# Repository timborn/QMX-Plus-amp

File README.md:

# QMX-amp
The QMX+ is a very nice radio kit from QPR Labs
https://qrp-labs.com/

This amp is designed by Ron Taylor, WA7GIL.  It should fit inside the empty
space in the case.

doc/original-drawings shows the original design sketchs

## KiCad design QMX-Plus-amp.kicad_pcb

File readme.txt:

Mon Nov 11 14:53:17 MST 2024
----------------------------
Changed the name of this project to QMX-Plus-amp to remove confusion with QMX.

Mon Aug 19 12:31:12 MST 2024
----------------------------
- silk screen is landing in all kinds of unhelpful places
- RF paths need wide copper.  How wide?  Figure out netclasses
- +12V probably needs a wide path as well for all that current (HOW MUCH?)
- want K1 & K2 to be *identical* even tho they appear in multiple schematic
  pages.  I want the control signals on one, and the RF paths on another.
  So far all I get are complaints about duplicate symbols, even when I 
  copy / paste special.

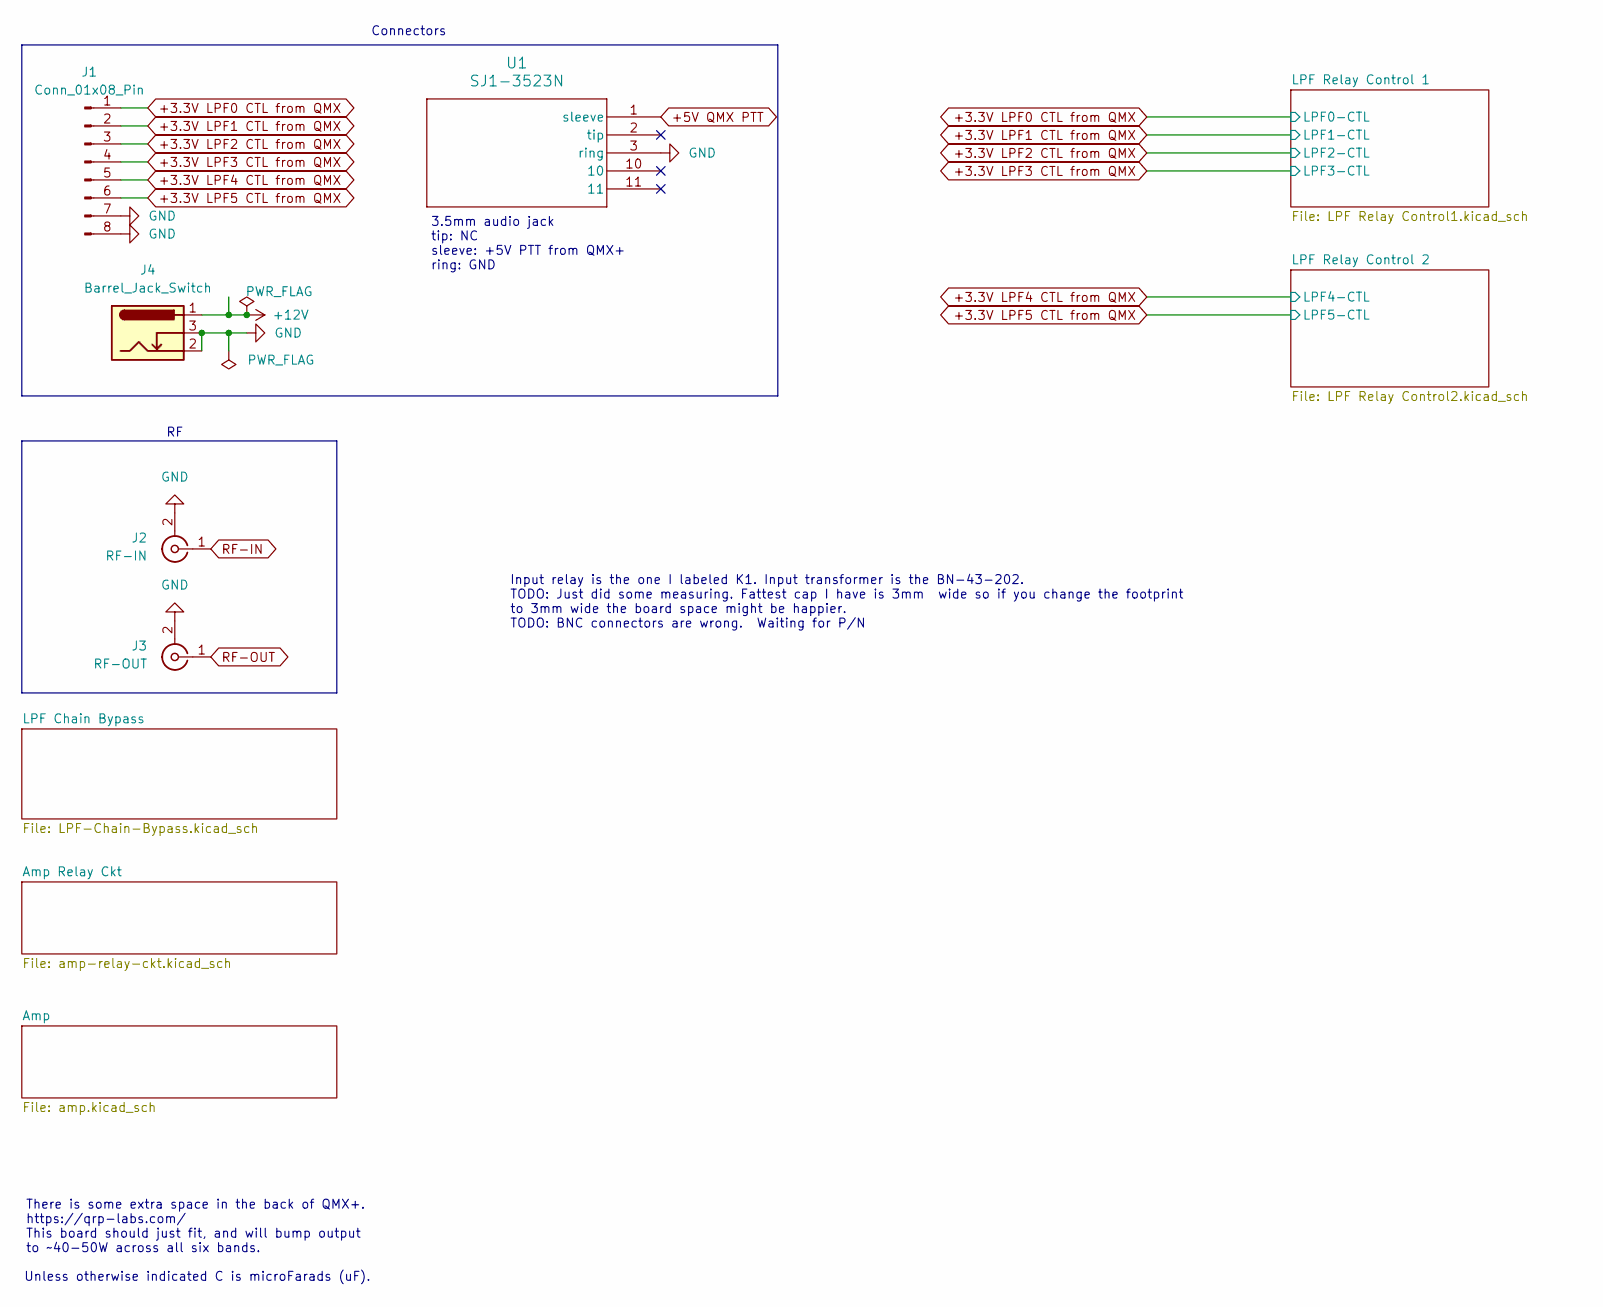
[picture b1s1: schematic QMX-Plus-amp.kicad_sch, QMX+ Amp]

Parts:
J1: Conn_01x08_Pin; PinHeader_1x08_P1.00mm_Horizontal
J2: RF-IN; BNC_Amphenol_B6252HB-NPP3G-50_Horizontal
J3: RF-OUT; BNC_Amphenol_B6252HB-NPP3G-50_Horizontal
J4: Barrel_Jack_Switch; BarrelJack_Horizontal
U1: SJ1-3523N; SJ1-3523N_CUD

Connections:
+3.3V LPF0 CTL from QMX: J1.1; also elsewhere on the board
+3.3V LPF1 CTL from QMX: J1.2; also elsewhere on the board
+3.3V LPF2 CTL from QMX: J1.3; also elsewhere on the board
+3.3V LPF3 CTL from QMX: J1.4; also elsewhere on the board
+3.3V LPF4 CTL from QMX: J1.5; also elsewhere on the board
+3.3V LPF5 CTL from QMX: J1.6; also elsewhere on the board
+5V QMX PTT: U1.1 (sleeve); also elsewhere on the board
+12V: J4.1; also elsewhere on the board
GND: J1.7, J1.8, J2.2 (Ext), J3.2 (Ext), J4.2, J4.3, U1.3 (ring); also elsewhere on the board
RF-IN: J2.1 (In); also elsewhere on the board
RF-OUT: J3.1 (In); also elsewhere on the board

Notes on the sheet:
Unless otherwise indicated C is microFarads (uF).
Connectors
Input relay is the one I labeled K1. Input transformer is the BN-43-202. TODO: Just did some measuring. Fattest cap I have is 3mm wide so if you change the footprint to 3mm wide the board space might be happier. TODO: BNC connectors are wrong. Waiting for P/N
3.5mm audio jack tip: NC sleeve: +5V PTT from QMX+ ring: GND
There is some extra space in the back of QMX+. https://qrp-labs.com/ This board should just fit, and will bump output to ~40-50W across all six bands.

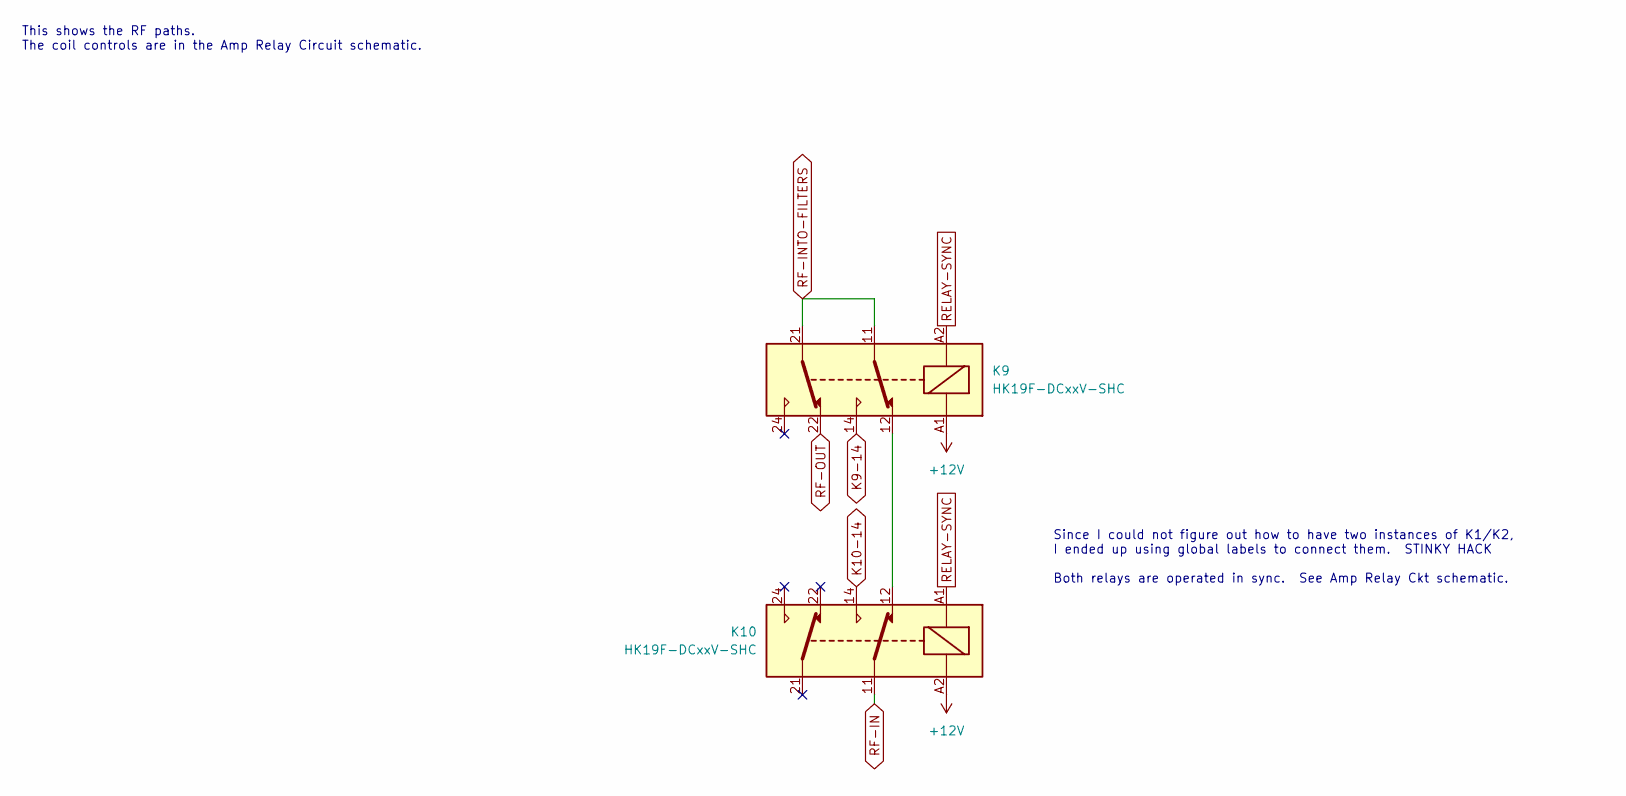
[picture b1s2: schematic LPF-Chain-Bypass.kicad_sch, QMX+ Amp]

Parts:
K9, K10: HK19F-DCxxV-SHC; Relay_DPDT_Finder_30.22

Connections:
+12V: K9.A1, K10.A2; also elsewhere on the board
K9-14: K9.14; also elsewhere on the board
K10-14: K10.14; also elsewhere on the board
unnamed: K9.12, K10.12
RELAY-SYNC: K9.A2, K10.A1; also elsewhere on the board
RF-IN: K10.11; also elsewhere on the board
RF-INTO-FILTERS: K9.11, K9.21; also elsewhere on the board
RF-OUT: K9.22; also elsewhere on the board

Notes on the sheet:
Since I could not figure out how to have two instances of K1/K2, I ended up using global labels to connect them. STINKY HACK Both relays are operated in sync. See Amp Relay Ckt schematic.
This shows the RF paths. The coil controls are in the Amp Relay Circuit schematic.

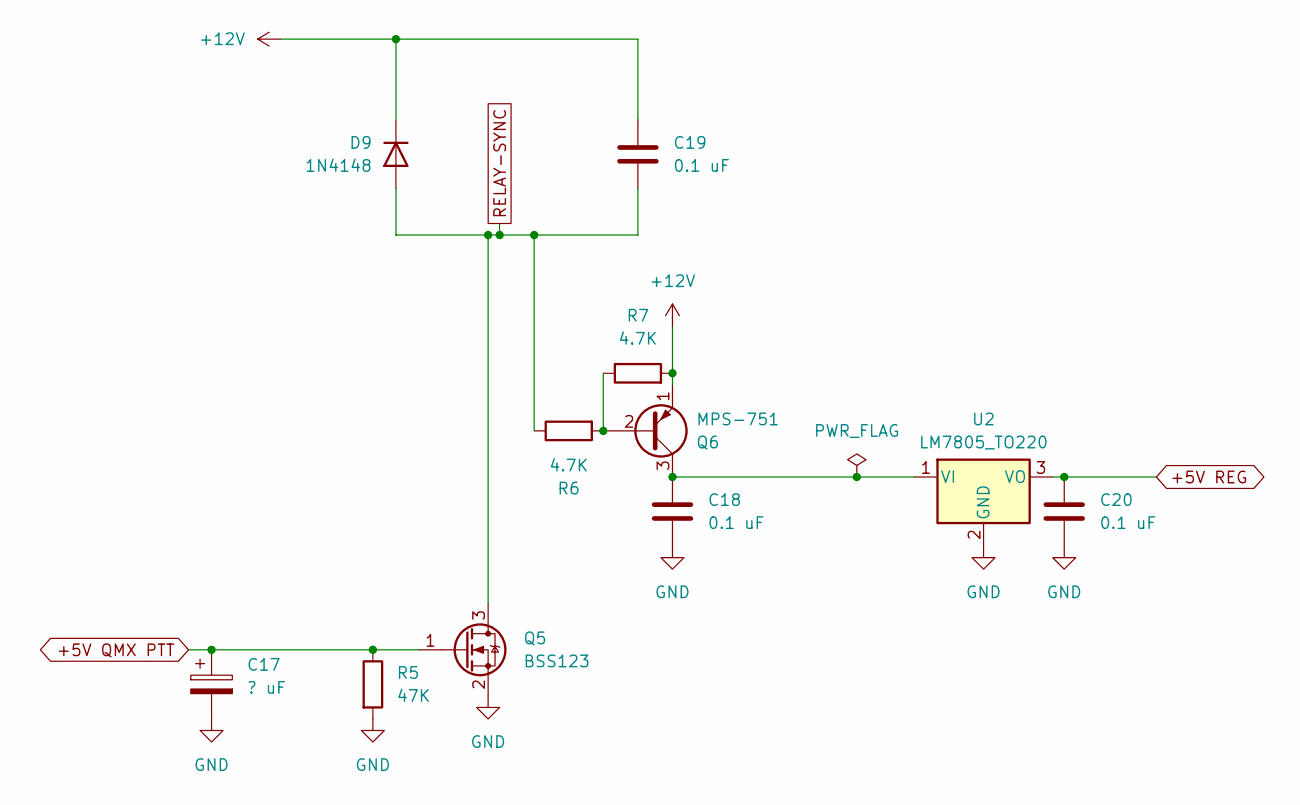
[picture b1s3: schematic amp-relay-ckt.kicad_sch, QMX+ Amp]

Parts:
C17: ? uF; C_Disc_D11.0mm_W3.0mm_P5.00mm
C18, C19, C20: 0.1 uF; R_0805_2012Metric_Pad1.20x1.40mm_HandSolder
D9: 1N4148; D_DO-34_SOD68_P7.62mm_Horizontal
Q5: BSS123; SOT-23
Q6: MPS-751; TO-92
R5: 47K; R_0805_2012Metric_Pad1.20x1.40mm_HandSolder
R6, R7: 4.7K; R_0805_2012Metric_Pad1.20x1.40mm_HandSolder
U2: LM7805_TO220; TO-220-3_Vertical

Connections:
+5V QMX PTT: C17.1, Q5.1 (G), R5.1; also elsewhere on the board
+5V REG: C20.1, U2.3 (VO); also elsewhere on the board
+12V: C19.1, D9.1 (K), Q6.1 (E), R7.2; also elsewhere on the board
GND: C17.2, C18.2, C20.2, Q5.2 (S), R5.2, U2.2 (GND); also elsewhere on the board
unnamed: Q6.2 (B), R6.2, R7.1
unnamed: C18.1, Q6.3 (C), U2.1 (VI)
RELAY-SYNC: C19.2, D9.2 (A), Q5.3 (D), R6.1; also elsewhere on the board

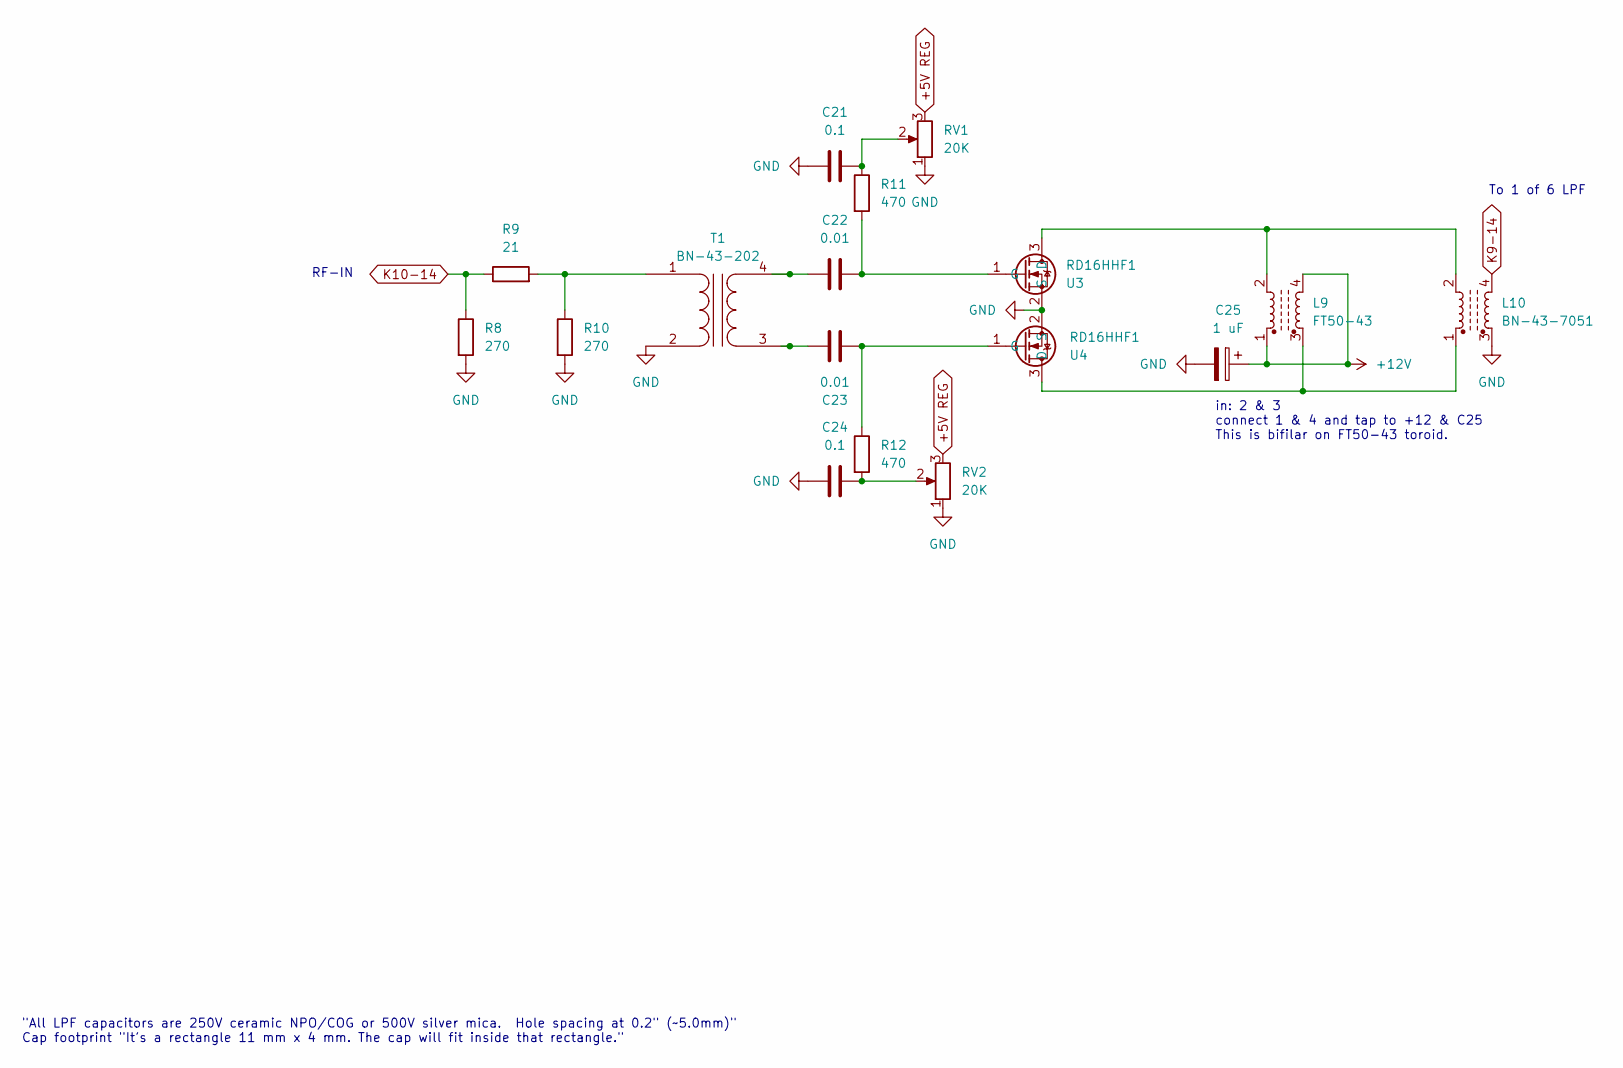
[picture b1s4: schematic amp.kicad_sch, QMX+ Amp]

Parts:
C21, C24: 0.1; R_0805_2012Metric_Pad1.20x1.40mm_HandSolder
C22, C23: 0.01; R_0805_2012Metric_Pad1.20x1.40mm_HandSolder
C25: 1 uF; C_Disc_D11.0mm_W3.0mm_P5.00mm
L9: FT50-43; Toroid_T50_Vertical_L14.0mm_W5.6mm_4pins
L10: BN-43-7051; BN-43-7051-FLAT
R8, R10: 270; R_Axial_DIN0207_L6.3mm_D2.5mm_P2.54mm_Vertical
R9: 21; R_Axial_DIN0207_L6.3mm_D2.5mm_P2.54mm_Vertical
R11, R12: 470; R_0805_2012Metric_Pad1.20x1.40mm_HandSolder
RV1, RV2: 20K; Potentiometer_Piher_PT-10-V05_Vertical
T1: BN-43-202; BN-43-202-FLAT
U3, U4: RD16HHF1; TO-220F-3_Horizontal_TabDown

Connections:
+5V REG: RV1.3, RV2.3; also elsewhere on the board
+12V: C25.1, L9.1, L9.4; also elsewhere on the board
GND: C21.1, C24.1, C25.2, L10.3, R8.2, R10.2, RV1.1, RV2.1, T1.2 (AB), U3.2 (S), U4.2 (S); also elsewhere on the board
K9-14: L10.4; also elsewhere on the board
K10-14: R8.1, R9.1; also elsewhere on the board
unnamed: C21.2, R11.1, RV1.2
unnamed: C24.2, R12.2, RV2.2
unnamed: R9.2, R10.1, T1.1 (AA)
unnamed: C23.1, T1.3 (SA)
unnamed: C22.1, T1.4 (SB)
unnamed: L9.2, L10.2, U3.3 (D)
unnamed: C22.2, R11.2, U3.1 (G)
unnamed: L9.3, L10.1, U4.3 (D)
unnamed: C23.2, R12.1, U4.1 (G)

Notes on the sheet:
To 1 of 6 LPF
"All LPF capacitors are 250V ceramic NPO/COG or 500V silver mica. Hole spacing at 0.2" (~5.0mm)" Cap footprint "It's a rectangle 11 mm x 4 mm. The cap will fit inside that rectangle."
RF-IN
in: 2 & 3 connect 1 & 4 and tap to +12 & C25 This is bifilar on FT50-43 toroid.

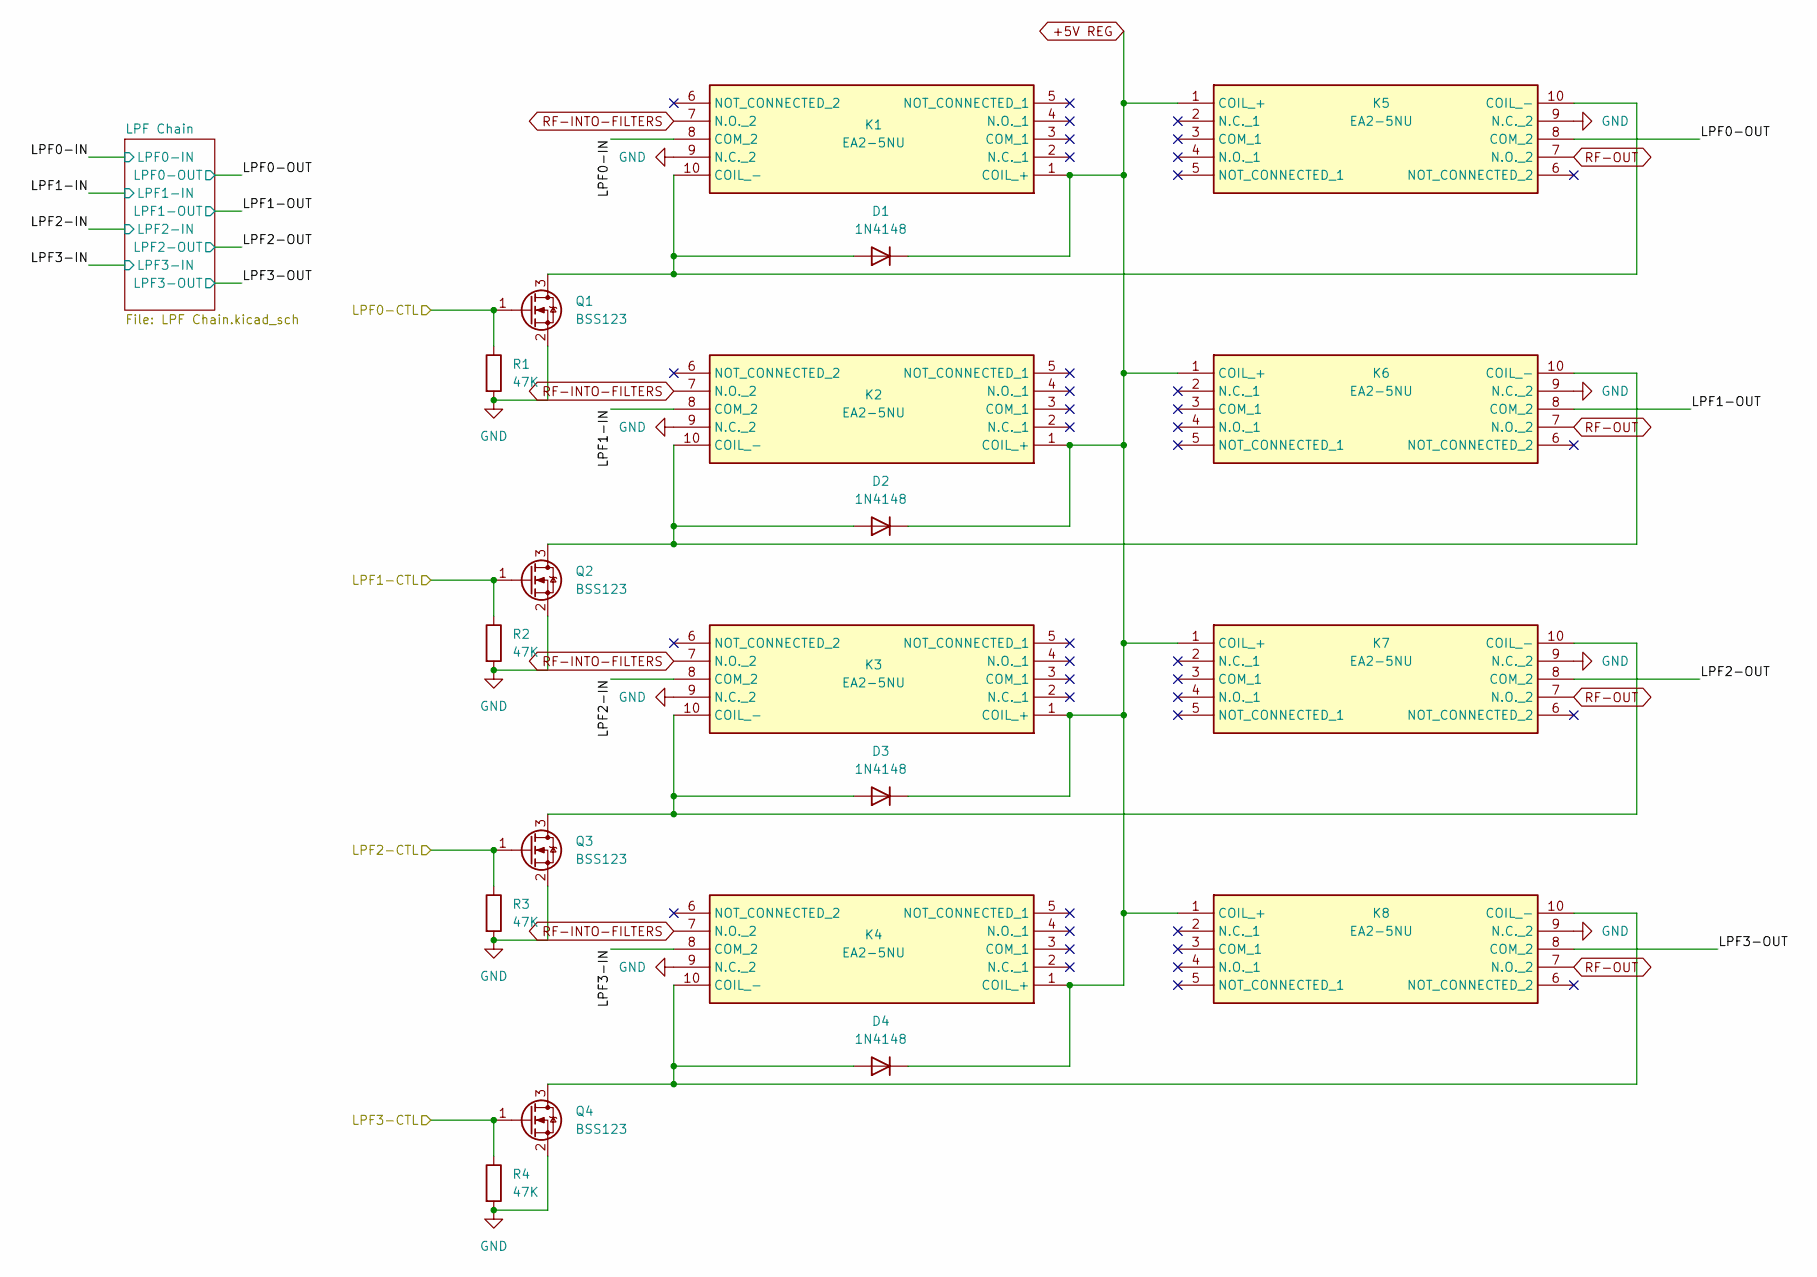
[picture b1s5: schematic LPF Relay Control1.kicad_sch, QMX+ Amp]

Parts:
D1, D2, D3, D4: 1N4148; D_DO-35_SOD27_P7.62mm_Horizontal
K1, K2, K3, K4, K5, K6, K7, K8: EA2-5NU; DIPS762W70P254L1420H540Q10N; Mouser Part Number 551-EA2-5NU
Q1, Q2, Q3, Q4: BSS123; SOT-23
R1, R2, R3, R4: 47K; R_0805_2012Metric_Pad1.20x1.40mm_HandSolder

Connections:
+3.3V LPF0 CTL from QMX: Q1.1 (G), R1.1; also elsewhere on the board
+3.3V LPF1 CTL from QMX: Q2.1 (G), R2.1; also elsewhere on the board
+3.3V LPF2 CTL from QMX: Q3.1 (G), R3.1; also elsewhere on the board
+3.3V LPF3 CTL from QMX: Q4.1 (G), R4.1; also elsewhere on the board
+5V REG: D1.1 (K), D2.1 (K), D3.1 (K), D4.1 (K), K1.1 (COIL_+), K2.1 (COIL_+), K3.1 (COIL_+), K4.1 (COIL_+), K5.1 (COIL_+), K6.1 (COIL_+), K7.1 (COIL_+), K8.1 (COIL_+); also elsewhere on the board
/LPF Relay Control 1/LPF0-IN: K1.8 (COM_2); also elsewhere on the board
/LPF Relay Control 1/LPF0-OUT: K5.8 (COM_2); also elsewhere on the board
/LPF Relay Control 1/LPF1-IN: K2.8 (COM_2); also elsewhere on the board
/LPF Relay Control 1/LPF1-OUT: K6.8 (COM_2); also elsewhere on the board
/LPF Relay Control 1/LPF2-IN: K3.8 (COM_2); also elsewhere on the board
/LPF Relay Control 1/LPF2-OUT: K7.8 (COM_2); also elsewhere on the board
/LPF Relay Control 1/LPF3-IN: K4.8 (COM_2); also elsewhere on the board
/LPF Relay Control 1/LPF3-OUT: K8.8 (COM_2); also elsewhere on the board
GND: K1.9 (N.C._2), K2.9 (N.C._2), K3.9 (N.C._2), K4.9 (N.C._2), K5.9 (N.C._2), K6.9 (N.C._2), K7.9 (N.C._2), K8.9 (N.C._2), Q1.2 (S), Q2.2 (S), Q3.2 (S), Q4.2 (S), R1.2, R2.2, R3.2, R4.2; also elsewhere on the board
unnamed: D1.2 (A), K1.10 (COIL_-), K5.10 (COIL_-), Q1.3 (D)
unnamed: D2.2 (A), K2.10 (COIL_-), K6.10 (COIL_-), Q2.3 (D)
unnamed: D3.2 (A), K3.10 (COIL_-), K7.10 (COIL_-), Q3.3 (D)
unnamed: D4.2 (A), K4.10 (COIL_-), K8.10 (COIL_-), Q4.3 (D)
RF-INTO-FILTERS: K1.7 (N.O._2), K2.7 (N.O._2), K3.7 (N.O._2), K4.7 (N.O._2); also elsewhere on the board
RF-OUT: K5.7 (N.O._2), K6.7 (N.O._2), K7.7 (N.O._2), K8.7 (N.O._2); also elsewhere on the board

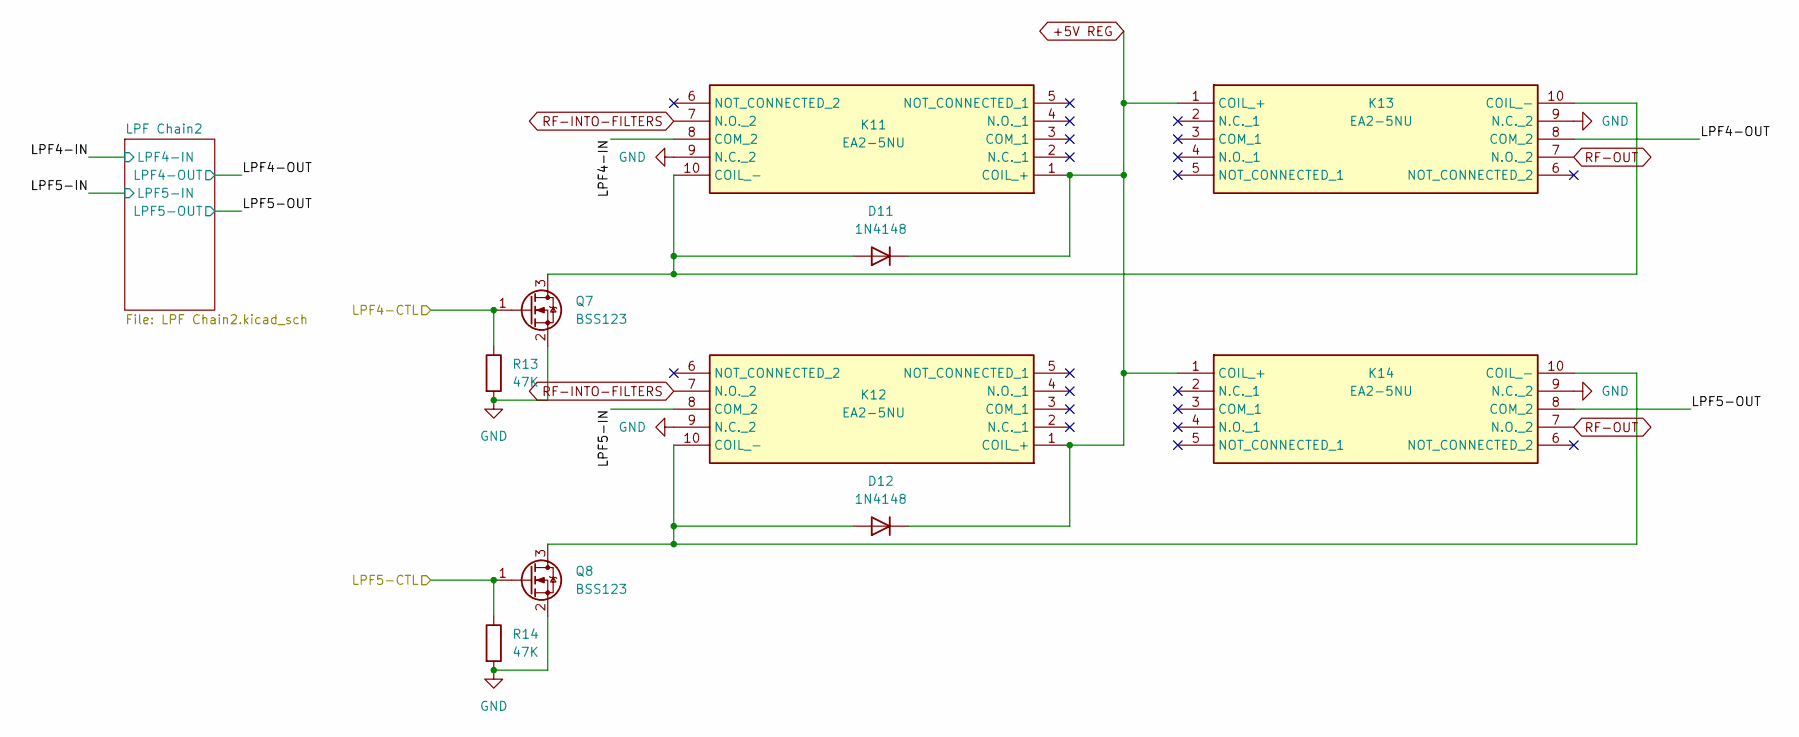
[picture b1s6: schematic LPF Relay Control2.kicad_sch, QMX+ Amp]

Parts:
D11, D12: 1N4148; D_DO-35_SOD27_P7.62mm_Horizontal
K11, K12, K13, K14: EA2-5NU; DIPS762W70P254L1420H540Q10N; Mouser Part Number 551-EA2-5NU
Q7, Q8: BSS123; SOT-23
R13, R14: 47K; R_0805_2012Metric_Pad1.20x1.40mm_HandSolder

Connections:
+3.3V LPF4 CTL from QMX: Q7.1 (G), R13.1; also elsewhere on the board
+3.3V LPF5 CTL from QMX: Q8.1 (G), R14.1; also elsewhere on the board
+5V REG: D11.1 (K), D12.1 (K), K11.1 (COIL_+), K12.1 (COIL_+), K13.1 (COIL_+), K14.1 (COIL_+); also elsewhere on the board
/LPF Relay Control 2/LPF4-IN: K11.8 (COM_2); also elsewhere on the board
/LPF Relay Control 2/LPF4-OUT: K13.8 (COM_2); also elsewhere on the board
/LPF Relay Control 2/LPF5-IN: K12.8 (COM_2); also elsewhere on the board
/LPF Relay Control 2/LPF5-OUT: K14.8 (COM_2); also elsewhere on the board
GND: K11.9 (N.C._2), K12.9 (N.C._2), K13.9 (N.C._2), K14.9 (N.C._2), Q7.2 (S), Q8.2 (S), R13.2, R14.2; also elsewhere on the board
unnamed: D11.2 (A), K11.10 (COIL_-), K13.10 (COIL_-), Q7.3 (D)
unnamed: D12.2 (A), K12.10 (COIL_-), K14.10 (COIL_-), Q8.3 (D)
RF-INTO-FILTERS: K11.7 (N.O._2), K12.7 (N.O._2); also elsewhere on the board
RF-OUT: K13.7 (N.O._2), K14.7 (N.O._2); also elsewhere on the board

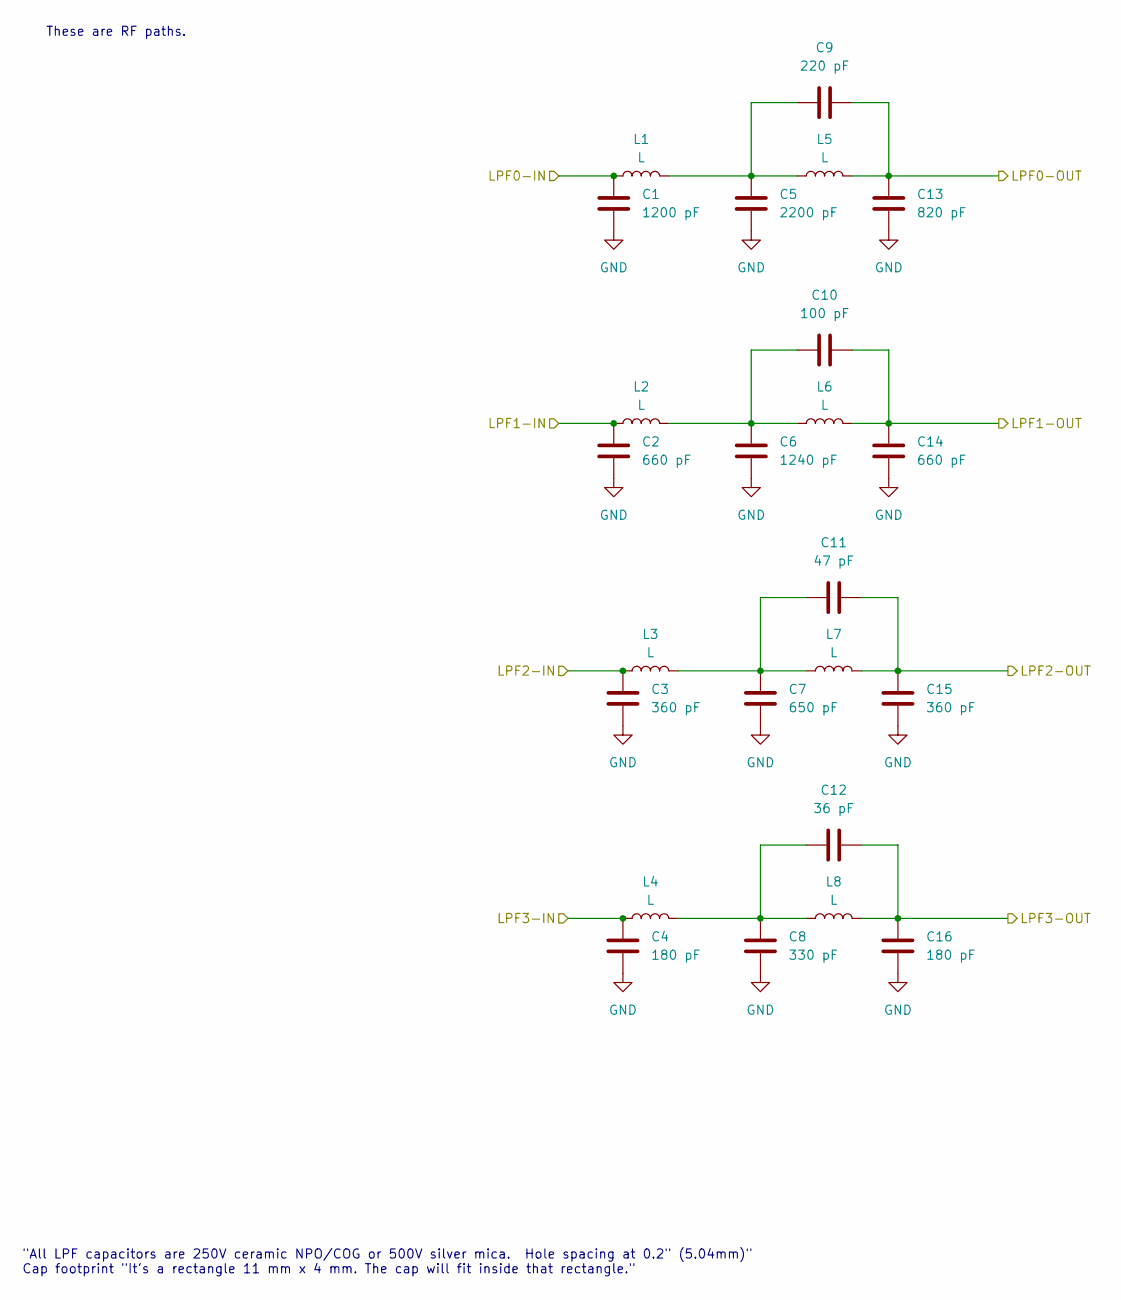
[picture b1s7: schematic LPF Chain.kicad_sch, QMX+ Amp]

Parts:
C1: 1200 pF; C_Disc_D11.0mm_W3.0mm_P5.00mm
C2, C14: 660 pF; C_Disc_D11.0mm_W3.0mm_P5.00mm
C3, C15: 360 pF; C_Disc_D11.0mm_W3.0mm_P5.00mm
C4, C16: 180 pF; C_Disc_D11.0mm_W3.0mm_P5.00mm
C5: 2200 pF; C_Disc_D11.0mm_W3.0mm_P5.00mm
C6: 1240 pF; C_Disc_D11.0mm_W3.0mm_P5.00mm
C7: 650 pF; C_Disc_D11.0mm_W3.0mm_P5.00mm
C8: 330 pF; C_Disc_D11.0mm_W3.0mm_P5.00mm
C9: 220 pF; C_Disc_D11.0mm_W3.0mm_P5.00mm
C10: 100 pF; C_Disc_D11.0mm_W3.0mm_P5.00mm
C11: 47 pF; C_Disc_D11.0mm_W3.0mm_P5.00mm
C12: 36 pF; C_Disc_D11.0mm_W3.0mm_P5.00mm
C13: 820 pF; C_Disc_D11.0mm_W3.0mm_P5.00mm
L1, L2, L3, L4, L5, L6, L7, L8: L; Toroid_T50_Vertical_L14.0mm_W5.6mm

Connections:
/LPF Relay Control 1/LPF0-IN: C1.1, L1.1; also elsewhere on the board
/LPF Relay Control 1/LPF0-OUT: C9.2, C13.1, L5.2; also elsewhere on the board
/LPF Relay Control 1/LPF1-IN: C2.1, L2.1; also elsewhere on the board
/LPF Relay Control 1/LPF1-OUT: C10.2, C14.1, L6.2; also elsewhere on the board
/LPF Relay Control 1/LPF2-IN: C3.1, L3.1; also elsewhere on the board
/LPF Relay Control 1/LPF2-OUT: C11.2, C15.1, L7.2; also elsewhere on the board
/LPF Relay Control 1/LPF3-IN: C4.1, L4.1; also elsewhere on the board
/LPF Relay Control 1/LPF3-OUT: C12.2, C16.1, L8.2; also elsewhere on the board
GND: C1.2, C2.2, C3.2, C4.2, C5.1, C6.2, C7.2, C8.2, C13.2, C14.2, C15.2, C16.2; also elsewhere on the board
unnamed: C5.2, C9.1, L1.2, L5.1
unnamed: C6.1, C10.1, L2.2, L6.1
unnamed: C7.1, C11.1, L3.2, L7.1
unnamed: C8.1, C12.1, L4.2, L8.1

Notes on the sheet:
These are RF paths.
"All LPF capacitors are 250V ceramic NPO/COG or 500V silver mica. Hole spacing at 0.2" (5.04mm)" Cap footprint "It's a rectangle 11 mm x 4 mm. The cap will fit inside that rectangle."

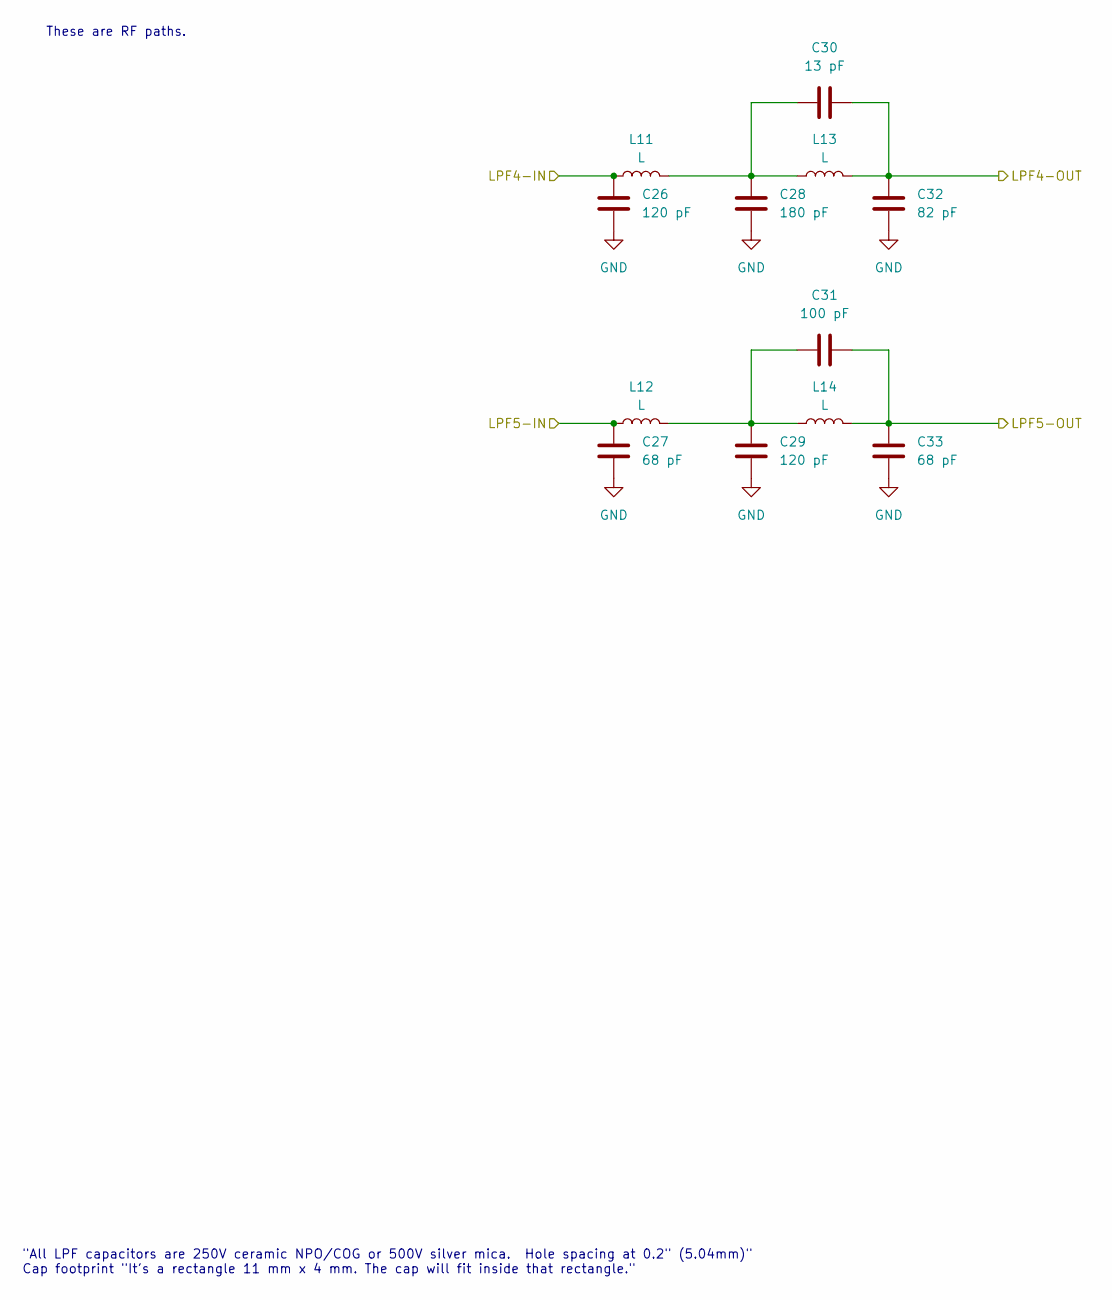
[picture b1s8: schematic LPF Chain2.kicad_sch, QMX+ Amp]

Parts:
C26, C29: 120 pF; C_Disc_D11.0mm_W3.0mm_P5.00mm
C27, C33: 68 pF; C_Disc_D11.0mm_W3.0mm_P5.00mm
C28: 180 pF; C_Disc_D11.0mm_W3.0mm_P5.00mm
C30: 13 pF; C_Disc_D11.0mm_W3.0mm_P5.00mm
C31: 100 pF; C_Disc_D11.0mm_W3.0mm_P5.00mm
C32: 82 pF; C_Disc_D11.0mm_W3.0mm_P5.00mm
L11, L12, L13, L14: L; Toroid_T50_Vertical_L14.0mm_W5.6mm

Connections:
/LPF Relay Control 2/LPF4-IN: C26.1, L11.1; also elsewhere on the board
/LPF Relay Control 2/LPF4-OUT: C30.2, C32.1, L13.2; also elsewhere on the board
/LPF Relay Control 2/LPF5-IN: C27.1, L12.1; also elsewhere on the board
/LPF Relay Control 2/LPF5-OUT: C31.2, C33.1, L14.2; also elsewhere on the board
GND: C26.2, C27.2, C28.1, C29.2, C32.2, C33.2; also elsewhere on the board
unnamed: C28.2, C30.1, L11.2, L13.1
unnamed: C29.1, C31.1, L12.2, L14.1

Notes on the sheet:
These are RF paths.
"All LPF capacitors are 250V ceramic NPO/COG or 500V silver mica. Hole spacing at 0.2" (5.04mm)" Cap footprint "It's a rectangle 11 mm x 4 mm. The cap will fit inside that rectangle."

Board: 2 copper layers, 101 parts (0 on the bottom side), 52 nets, no tracks yet.

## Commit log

2024-08-05 PCB template now fits the QMX dead space
2024-08-05 added scans of original design
2024-08-05 starting working on schematic. struggling with relays
2024-08-07 made some progress on LPF Relay Control sheet. Looks like it will span two sheets
2024-08-08 Working on LPF control and actual filters. They are intertwingled pretty tightly. Also ran ERC and beat out some errors.
2024-08-08 moved LPF0 to LPF as I can fit them all into one schematic
2024-08-08 rm LPF0.kicad_sch now that it's been moved
2024-08-08 placed LPF chains in sub-schematic. ERC passes
2024-08-09 checkpoint progress, working on LPF chains
2024-08-09 fleshed out LPF chains. ERC passes
2024-08-09 added RF through LPF chains
2024-08-09 worked on strange stuff on btm of LPF filter chain schematic. ERC passes
2024-08-09 LPF chains, all caps now normal; missing inducator added. ERC passes
2024-08-10 last of v0.1. Ron stopped by with many corrections for me
2024-08-10 all caps on LPF Chain are pF. rest are uF
2024-08-10 RF-IN-PAST-SW now RF-INTO-FILTERS
2024-08-10 I think all the caps have units now
2024-08-10 does NOT pass ERC. Something going on with LM7805
2024-08-10 +5V REG now connected to all LPF relay coils
2024-08-10 trying to get K1 & K2 appear in multiple places, yet be recognized as identical. Currently reporting dup K1
2024-08-10 started readme.txt to keep track of some of these changes
2024-08-11 checkpoint progress from 240810
2024-08-11 changed +5V and +12V from global symbol to the more normal voltage busses
2024-08-11 could not figure out how to have two instances of K1 so I used global labels. STINKY HACK
2024-08-11 added cap values to filter chain per Ron
2024-08-11 ERC passes again. The transistor in front of LM7805 is a switch, so PWR_FLAG doesn't cross over unless I'm explicit
2024-08-11 rm amp.kicad_sch. Vestigial. Interfering with progress
2024-08-12 checkpoint progress from Sunday 240811
2024-08-12 imported BN-43-202 symbol and footprint into ZZZMyLibrary
2024-08-12 working on Amp. Stuck on symbol for RD16HHF1
2024-08-12 modeled RD16HHF1 and added it to Amp. ERC passes
2024-08-12 first pass at amp ckt. had to create a few parts, so these should be checked VERY carefully
2024-08-12 changed symbol for RD16HHF1 to be more like BSS123, per Ron
2024-08-12 got rid of K11 which was alias for K2. Figured out RELAY-SYNC as a way of making sure K1 & K2 operate in sync
2024-08-13 v0.5
2024-08-13 v0.6 ERC passes. I went over it with a fine tooth comb and corrected lots of little stuff. Ron should review all the components I have to create very carefully. In particular, MPS-751 symbol does not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
2024-08-13 v0.7 fixed MPS-751 and bifilar on FT50-43. ERC passes
2024-08-14 gave RD16HHF1 an TO-220 footprint
2024-08-14 started picking parts. had to create T50 schamtic, footprint and 3D model.
2024-08-18 I think I am working on picking parts
2024-08-18 created 11x4mm footprint with 5mm pin spacing for caps on LPF per Ron
2024-08-18 ron came by and gave lots of feedback. many notes on schematic for additional changes
2024-08-19 checkpoint changes
2024-08-19 v0.8 after much hacking of BS audio footprint from Digikey we now have a 3.5mm audio jack wired in. ERC pass
2024-08-19 expended to all 6 LPFs. ERC pass. Need to check component values on new LPF page
2024-08-19 v0.9 ERC passes. All parts have footprints. Need to renumber pages so things related are closer in printout
2024-08-19 checkpoint before I shrink width of capps so things might fit PCB
2024-08-19 v0.10 after slimming down capacitor width to 3mm so it *barely* fits.
2024-08-20 whatever changes happened?
2024-08-20 Ron helped moved all the parts into PCB
2024-08-22 worked on netclasses for 12VPWR and RF
2024-11-11 Proper name is QMX+, not QMX.
2024-11-11 updated to explain QMX-Plus-amp
2024-11-11 finish renaming to QMX-Plus-amp
